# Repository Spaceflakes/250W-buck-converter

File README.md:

# PUDGALA 300
### High-Power-Density 250W Synchronous Buck Converter (28V–60V In → 24.88V @ 10A Out)

> *"Ex umbra, in solem."* — [HEX Aerospace](https://hexaerospace.in)

---

## Overview & Motivation

The **PUDGALA 300** is an open-source, high-power-density synchronous buck converter developed with [HEX Aerospace](https://hexaerospace.in). It steps down wide-range DC voltages (nominal 36V–54V battery buses, 7S–14S LiPo / Li-ion packs) down to a regulated **24.88V (25V / 24V compatible)** rail delivering **10A continuous (250W nominal)**, and has been bench-tested up to **12.5A continuous (~312W)** with peak efficiency exceeding **96%**.

### Field FPV Charging
The primary motivation for this project was powering high-power FPV drone battery chargers directly from repurposed **13S electric scooter (E-scooter) battery packs** in the field.

* **The Problem:** 13S Li-ion battery packs swing from **39.0V** (empty) to **54.6V** (fully charged). However, most popular field chargers (such as ISDT, ToolkitRC, Hota, and SkyRC) have a maximum input voltage limit of **30.0V DC**. Connecting a 13S battery directly would instantly destroy the charger.
* **The Solution:** The PUDGALA 300 steps down the 39V–54.6V input into a stable **24.88V** rail at up to **10A–12.5A (>300W)**. This allows pilots to rapidly parallel-charge multiple 6S drone packs in the field using salvaged e-mobility batteries.

---

> [!CAUTION]
> ### Critical Operational Notice: Anti-Spark Connectors & Inrush Caution
> During early testing of the prototype, the board was connected to a high-voltage 13S battery (~54.6V) with an active load already plugged into the output. The raw XT60 connector sparked violently upon contact, and the severe inrush arc and inductive voltage spike exceeded the MOSFET breakdown rating, killing one of the switching FETs.
>
> **Mandatory Safe Operating Procedures:**
> 1. **Always Use Anti-Spark Connectors:** When connecting sources above 30V (especially 13S / 48V–54.6V packs), use an anti-spark connector with a built-in pre-charge resistor (such as **XT90-S** or **XT60-S**) or an external pre-charge switch.
> 2. **Power-On Sequence:** Always connect the battery input **first** with no output load connected. Confirm the output power indicator LED is on (verifying stable 24.88V regulation) **before** plugging in your charger.
> 3. **Lead Length:** Keep input battery leads as short as possible to minimize parasitic wiring inductance.

---

## Key Specifications

| Parameter | Specification | Notes / Conditions |
| :--- | :--- | :--- |
| **Input Voltage** | **28.0V to 60.0V DC** | Designed for 13S E-scooter packs (39V–54.6V), 7S–14S LiPo, 36V/48V buses |
| **Output Voltage** | **24.88V nominal (~25V)** | Calibrated via precision feedback divider (301 kΩ / 10 kΩ) |
| **Continuous Output Current** | **10.0 A (Nominal) / 12.5 A (Tested)** | 250W nominal; bench-tested to 312W continuous (requires active cooling) |
| **Peak / Overcurrent Limit** | **12.0 A peak** | Cycle-by-cycle limit with automatic hiccup restart |
| **Continuous Output Power** | **250 W nominal (up to 312 W)** | High continuous power density in a pocket-sized 50×50 mm board |
| **Switching Frequency** | **~1.0 MHz (966 kHz nominal)** | Programmed via 9.09 kΩ resistor |
| **Peak Efficiency** | **> 96%** | Typically 94.5%–96.2% across 36V–52V input range |
| **PCB Dimensions** | **50.0 mm × 50.0 mm × 12.0 mm** | Low profile; horizontal bent-lead electrolytic capacitors |
| **PCB Layer Stackup** | **6 Layers (1 oz / 35 µm Cu each)** | Solid internal GND reference planes on L2 & L5 |
| **Connectors** | **AMASS XT30PW-M (Right-Angle)** | High-current, vibration-resistant power in/out connectors |
| **Auxiliary Fan Header** | **2-pin test points (+Fan / -Fan)** | 24V regulated output for an active cooling fan |
| **Enclosure** | **CAD STEP File Coming Soon** | 3D-printable / CNC enclosure in progress |

---

## System Architecture & Block Diagram

```mermaid
flowchart LR
    subgraph Input_Stage ["Input Stage (13S Battery: 39V - 54.6V)"]
        BATT["13S E-Scooter Pack\n(Anti-Spark XT90-S)"] --> J1["Power In\nXT30PW-M"]
        J1 --> D2["TVS Surge Clamp\nSMBJ60A (60V)"]
        D2 --> C_IN_BULK["Bulk Damping\n47µF Elec. (C9)"]
        C_IN_BULK --> C_IN_HF["High-Freq MLCC\n2x 22µF 2220 + 100nF"]
    end

    subgraph Power_Stage ["Synchronous Buck Stage"]
        C_IN_HF --> Q1["High-Side NexFET\nCSD19534Q5A (100V)"]
        Q1 --> SW["Switch Node (SW)"]
        Q2["Low-Side Sync NexFET\nCSD19502Q5B (80V, 2.8mΩ)"] --- SW
        SW --> L1["Molded Power Choke\n2.2µH 20A (BMRF)"]
        L1 --> RSENSE["Current Shunt\n5mΩ 2512 (R3)"]
    end

    subgraph Controller_Loop ["Control & Protection (LM5149-Q1)"]
        U1["TI LM5149-Q1\nSync Controller"] -.->|HO Drive| Q1
        U1 -.->|LO Drive| Q2
        RSENSE -.->|Kelvin ISNS±| U1
        U1 -.->|DRSS Active| R2["CNFG: 40.2kΩ"]
        U1 -.->|1 MHz Osc| R1["RT: 9.09kΩ"]
        U1 -.->|PFM / Diode Emul.| VDDA["VDDA"]
    end

    subgraph Output_Stage ["Output Filtering & Protection (24.88V / 10A-12.5A)"]
        RSENSE --> C_OUT_HF["MLCC Bank\n4x 10µF 1210"]
        C_OUT_HF --> C_OUT_BULK["Output Bulk\n220µF Elec. (C10)"]
        C_OUT_BULK --> D3["OVP TVS Clamp\nSMBJ28A (28V)"]
        D3 --> FB_DIV["Feedback Divider\n301kΩ / 10kΩ"] -.->|FB| U1
        D3 --> LED_IND["Power Good LED\n(D1 + R8 11.5k)"]
        D3 --> J2["Power Out\nXT30PW-M"] --> CHARGER["FPV Charger\n(< 30V Input Limit)"]
        D3 --> FAN_HDR["Fan Header\n(+Fan / -Fan)"]
    end

    classDef stage fill:#1e1e24,stroke:#4a90e2,stroke-width:2px,color:#ffffff;
    classDef controller fill:#2c3e50,stroke:#e74c3c,stroke-width:2px,color:#ffffff;
    class Input_Stage,Power_Stage,Output_Stage stage;
    class Controller_Loop controller;
```

---

## Component Analysis & IC Explanations

### 1. Primary Controller: Texas Instruments LM5149-Q1 (`U1`)
The **LM5149-Q1** (`PLM5149QRGYRQ1`) is an AEC-Q100 qualified, 80V/100V-capable synchronous buck DC-DC controller designed for high-efficiency, low-EMI industrial and automotive applications.
* **Dual-Random Spread Spectrum (DRSS):** Programmed via a 40.2 kΩ resistor (`R2`) on the `CNFG` pin. DRSS modulates the switching frequency to spread out noise energy and lower peak EMI spikes.
* **1.0 MHz Switching Frequency:** Set via a 9.09 kΩ resistor (`R1`) on the `RT` pin (~966 kHz nominal). Running at 1 MHz allows using a small 2.2 µH inductor and compact ceramic capacitors while keeping transient response fast.
* **PFM / Light-Load Efficiency:** The `PFM/SYNC` pin is tied directly to `VDDA`. Under light or no-load conditions, the controller automatically enters diode emulation to reduce idle battery drain.
* **Current Sensing & Protection:** Cycle-by-cycle current limiting using differential sense inputs (`ISNS+` and `VOUT/ISNS-`) across the shunt resistor, cutting off overcurrents at 12A with automatic hiccup restart under short circuits.
* **Gate Drivers & Internal VCC:** Built-in 5V regulator with a 2.2 µF bypass capacitor (`C8`), providing strong gate drive currents and adaptive deadtime control to prevent shoot-through.

---

### 2. High-Side Power MOSFET: TI CSD19534Q5A (`Q1`)
* **Package:** SON 5 mm × 6 mm (TDSON-8)
* **Key Ratings:** 100V, 44A continuous, 10.3 mΩ typical on-resistance
* **Why this part:** Chosen for its ultra-low gate charge (13.8 nC). At a high 1.0 MHz switching frequency, low gate charge is critical to keep switching losses minimal.

---

### 3. Low-Side Synchronous Rectifier MOSFET: TI CSD19502Q5B (`Q2`)
* **Package:** SON 5 mm × 6 mm (TDSON-8)
* **Key Ratings:** 80V, 138A, ultra-low 2.8 mΩ typical on-resistance
* **Why this part:** The low-side switch handles freewheeling current roughly 50% of the time. Its tiny 2.8 mΩ resistance keeps conduction heat minimal (~0.15W at 10A), allowing it to run cool without extra heatsinks.

---

### 4. Power Inductor: Chilisin BMRF00101040 (`L1`)
* **Value:** 2.2 µH, 20A saturation current
* **Why this part:** High 20A saturation rating provides clean headroom above the 12A peak limit. The fully shielded composite iron-powder core prevents radiated magnetic noise from interfering with nearby electronics.

---

### 5. Current Sense Shunt: 5 mΩ Metal Element 2512 (`R3`)
* **Value:** 5 mΩ (0.005 Ω), 1% tolerance, 2512 package
* **Operation:** Senses output current directly. Paired with the controller's 60 mV threshold, it sets the cycle-by-cycle peak limit to 12.0A. Connected using 4-wire Kelvin traces (`NT1`, `NT2`) to avoid PCB trace resistance errors.

---

### 6. Protection Clamps: SMBJ60A & SMBJ28A TVS Diodes
* **Input TVS (`D2` — SMBJ60A):** 60V standoff voltage clamp that absorbs inductive voltage spikes when connecting or disconnecting the battery.
* **Output TVS (`D3` — SMBJ28A):** 28V standoff voltage clamp that prevents the output from ever exceeding the 30V maximum input rating of downstream FPV chargers.
* **Fuse Recommendation:** Always install an inline 15A fuse on the positive battery lead (or use a battery pack with a short-circuit-protected BMS). If an overvoltage fault occurs, the TVS clamps the rail to ground and blows the fuse instantly, ensuring the charger never sees excessive voltage.

---

### 7. Capacitor Filtering Network
* **Input Bank:** Two 22 µF 2220 MLCCs (`C1`, `C2`) for high-frequency ripple, a 100 nF MLCC (`C14`) right at the high-side FET drain, and a 47 µF horizontal electrolytic (`C9`) to damp input line ringing.
* **Output Bank:** Four 10 µF 1210 MLCCs (`C4`, `C11`, `C12`, `C13`) yielding 40 µF of ultra-low ESR capacitance for low voltage ripple, plus a 220 µF horizontal electrolytic (`C10`) for transient load response.

---

## Operating Limits & Thermal Behavior

### 1. Continuous 12.5A Bench Testing
The PUDGALA 300 was successfully tested on the bench at **12.5 A continuous** at ~24.9V, delivering **~312 W output power**:
* **Thermal Rise:** Resistive heating increases significantly (+56%) when stepping up from 10A to 12.5A. In open still air at 12.5A, the bare board components quickly reach 90°C–100°C.
* **Cooling Requirement:** While the board handles 12.5A electrically, **active forced airflow or heatsink coupling is mandatory** for sustained operation above 10A.

### 2. Cooling Options
1. **Passive Air:** Suitable for continuous loads up to **100W–120W** (around 4A–5A).
2. **Forced Air Cooling:** Full **250W–300W+ continuous** rating when a 24V cooling fan is connected to the onboard `+Fan / -Fan` solder pads.
3. **Chassis / Heatsink Mounting:** The bottom side of the PCB has **no components** ("*Yes, there's nothing on this side*"). A 1.0 mm thermal silicone pad placed between the bottom ground plane and an aluminum enclosure or frame allows sinking heat directly into external metal.
4. **Protective Enclosure:** A custom 3D-printable / CNC enclosure STEP model with fan mounting and heatsink interface will be uploaded to this repository soon.

---

## 6-Layer PCB Stackup & Layout

The board uses a custom 6-layer FR4 stackup (1.6 mm thickness, 1 oz / 35 µm copper across all layers) optimized for low loop inductance and thermal dissipation.

| Layer | Type | Material | Thickness | Description & Key Nets |
| :--- | :--- | :--- | :--- | :--- |
| **Top (Layer 1)** | Copper | 1 oz Cu | 35 µm | Components, switching loop, gate drives, analog ground (`F.Cu`) |
| *Dielectric 1* | Prepreg | FR4 | 100 µm (0.10 mm) | Ultra-thin dielectric for tight RF coupling to ground |
| **Inner 1 (Layer 2)** | Copper | 1 oz Cu | 35 µm | **Solid Ground Plane** — immediate return path under L1 (`In1.Cu`) |
| *Dielectric 2* | Core | FR4 | 535 µm (0.535 mm) | Internal structural core |
| **Inner 2 (Layer 3)** | Copper | 1 oz Cu | 35 µm | Ground & auxiliary shielding plane (`In2.Cu`) |
| *Dielectric 3* | Prepreg | FR4 | 100 µm (0.10 mm) | Prepreg isolation layer |
| **Inner 3 (Layer 4)** | Copper | 1 oz Cu | 35 µm | **Power Planes** — +BATT input & +24V distribution (`In3.Cu`) |
| *Dielectric 4* | Core | FR4 | 535 µm (0.535 mm) | Internal structural core |
| **Inner 4 (Layer 5)** | Copper | 1 oz Cu | 35 µm | **Solid Ground Plane** — plane shielding & thermal spreading (`In4.Cu`) |
| *Dielectric 5* | Prepreg | FR4 | 100 µm (0.10 mm) | Prepreg isolation layer |
| **Bottom (Layer 6)** | Copper | 1 oz Cu | 35 µm | **Flat Ground Plane** — zero components, heatsink interface (`B.Cu`) |

*Total Board Thickness: 1.6 mm*

---

## Hardware Gallery

### Assembled & Bare PCB
| Populated SMD Board | Bare 6-Layer ENIG PCB |
| :---: | :---: |
|  |  |
| *Reflowed SMD components on hotplate* | *Bare 50x50 mm board with ENIG finish* |

### PCB Artwork & Stencil Inspection
| Copper Signature Detail | Silkscreen Motto & Fan Header | Solder Paste Deposition (Microscope) |
| :---: | :---: | :---: |
|  |  |  |
| *"Sid J" etched in top copper* | *"Ex umbra, in solem." & fan pads* | *Solder paste stencil on VQFN-24* |

### 3D CAD Renders & Schematic
| Isometric 3D View | Top Component Placement | Bottom Heatsink Plane |
| :---: | :---: | :---: |
|  |  |  |
| *3D isometric view* | *Component layout* | *Flat ground interface* |

> 📄 **Schematic:** Full vector schematic available at [`images/schematic.svg`](images/schematic.svg).

---

## Bill of Materials (BOM)

All components are standard, readily sourcable parts with matching **LCSC Part Numbers** for turn-key assembly via JLCPCB, PCBWay, or other assembly houses.

| Designator | Value / Part | Description | Package / Footprint | Qty | LCSC Part # |
| :--- | :--- | :--- | :--- | :---: | :--- |
| **U1** | **PLM5149QRGYRQ1** | TI 80V/100V Synchronous Buck DC-DC Controller with DRSS | VQFN-24 (4.5×3.5mm) | 1 | **C7528454** |
| **Q1** | **CSD19534Q5A** | TI 100V 44A 10.3mΩ N-Ch NexFET (High-Side Switch) | TDSON-8 / SON 5×6mm | 1 | **C114200** |
| **Q2** | **CSD19502Q5B** | TI 80V 138A 2.8mΩ N-Ch NexFET (Low-Side Sync Rectifier) | TDSON-8 / SON 5×6mm | 1 | **C2864118** |
| **L1** | **2.2u, 20A** | Chilisin BMRF00101040 Shielded Power Inductor | SMD 10×10×4.0mm | 1 | **C3002681** |
| **R3** | **5m (0.005Ω)** | Current Sense Shunt Resistor, 1%, 2W/3W | SMD 2512 | 1 | **C48982662** |
| **D2** | **SMBJ60A** | 600W 60V Unidirectional TVS Surge Diode | DO-214AA (SMB) | 1 | *Standard* |
| **D3** | **SMBJ28A** | 600W 28V Unidirectional TVS Overvoltage Diode | DO-214AA (SMB) | 1 | *Standard* |
| **J1** | **Power In** | AMASS XT30PW-M Right-Angle 2-Pin Male Connector | XT30PW-M Horizontal | 1 | *Standard* |
| **J2** | **Power Out** | AMASS XT30PW-M Right-Angle 2-Pin Male Connector | XT30PW-M Horizontal | 1 | *Standard* |
| **C1, C2** | **22u** | Ceramic Capacitor, 50V/100V, X7R | SMD 2220 | 2 | **C7499406** |
| **C4, C11, C12, C13** | **10u** | Ceramic Capacitor, 35V/50V, X7R | SMD 1210 | 4 | **C77102** |
| **C9** | **47u** | Low-ESR Radial Aluminum Electrolytic, 63V/100V (Horizontal) | Rad 8×15mm Horizontal | 1 | **C5110663** |
| **C10** | **220u** | Low-ESR Radial Aluminum Electrolytic, 35V/50V (Horizontal) | Rad 10×16mm Horizontal | 1 | **C95082** |
| **C3** | **100n** | Bootstrap Capacitor (CBOOT), 50V, X7R | SMD 0603 | 1 | **C15725** |
| **C14** | **100n** | High-Frequency Input Bypass, 100V, X7R | SMD 0603 | 1 | **C7499406** |
| **C5** | **1u** | VDDA Analog Bypass Capacitor, 16V, X7R | SMD 0402 | 1 | **C29266** |
| **C6** | **680p** | Loop Compensation Zero Capacitor, 50V, C0G/X7R | SMD 0402 | 1 | *Standard* |
| **C7** | **24p** | Loop Compensation HF Pole Capacitor, 50V, C0G | SMD 0402 | 1 | **C2171081** |
| **C8** | **2.2u** | VCC Gate Drive Bias Bypass, 16V, X7R | SMD 0805 | 1 | **C170101** |
| **R1** | **9k09 (9.09kΩ)** | Switching Frequency Resistor (1% tolerance, sets ~1MHz) | SMD 0402 | 1 | **C861611** |
| **R2** | **40k2 (40.2kΩ)** | Mode & Dual-Random Spread Spectrum Resistor (1%) | SMD 0402 | 1 | **C491131** |
| **R4** | **301k (301kΩ)** | Feedback Voltage Divider Upper Resistor (0.5% or 1%) | SMD 0402 | 1 | **C2981491** |
| **R5** | **10k (10.0kΩ)** | Feedback Voltage Divider Lower Resistor (0.5% or 1%) | SMD 0402 | 1 | **C95204** |
| **R6** | **5k9 (5.9kΩ)** | External Error Amplifier Compensation Resistor (1%) | SMD 0402 | 1 | **C491142** |
| **R7** | **100k (100kΩ)** | Power Good (PG) Pull-Up Resistor (1%) | SMD 0402 | 1 | **C122538** |
| **R8** | **11k5 (11.5kΩ)** | LED Current Limiting Ballast Resistor (~2mA @ 24V) | SMD 0805 | 1 | *Standard* |
| **D1** | **LED** | Green / Blue Status Indicator LED | SMD 0603 | 1 | **C46610608** |
| **+FAN, -FAN** | **+Fan / -Fan** | Keystone 5015 Micro-Mini Solder Test Points | TP Keystone 5015 | 2 | *Standard* |
| **H1, H2, H3, H4** | **M3 Holes** | Mounting Holes with Grounded Annular Pad & Via Array | 3.2mm M3 Pad | 4 | *Mechanical* |
| **NT1, NT2, NT3** | **NetTie_2** | Kelvin-Sense & AGND Star Ground Isolation Net Ties | Net Tie SMD | 3 | *PCB Feature* |

> An interactive browser-based BOM with cross-probing component highlighting is located at [`250W Bat/bom/ibom.html`](250W%20Bat/bom/ibom.html).

---

## Manufacturing & Fabrication Guide

### PCB Fabrication Parameters
* **Layers:** 6
* **Board Dimensions:** 50.0 mm × 50.0 mm
* **Corner Radius:** 4.0 mm
* **PCB Thickness:** 1.6 mm
* **Copper Weight:** 1 oz outer / 1 oz inner (35 µm Cu across all 6 layers)
* **Surface Finish:** ENIG (Electroless Nickel Immersion Gold) recommended for high-current pads and flat thermal contact; Lead-Free HASL is acceptable.
* **Solder Mask:** Green (or Matte Black)
* **Silkscreen:** White
* **Minimum Trace / Space:** 0.15 mm / 0.15 mm (6 mil / 6 mil)
* **Minimum Drill:** 0.3 mm (via hole) / 0.5 mm (via pad)

### Production Files
All fabrication and assembly deliverables are located in the [`250W Bat/production/`](250W%20Bat/production/) directory:
* **Gerbers & Drill Archive:** [`250W_Bat.zip`](250W%20Bat/production/250W_Bat.zip)
* **BOM File:** [`bom.csv`](250W%20Bat/production/bom.csv)
* **Pick-and-Place (CPL) Centroid:** [`positions.csv`](250W%20Bat/production/positions.csv)
* **Netlist:** [`netlist.ipc`](250W%20Bat/production/netlist.ipc)
* **3D CAD STEP Model:** [`Converter.step`](250W%20Bat/Converter.step) & [`board.step`](250W%20Bat/board.step)

---

## Repository Structure

```
├── LICENSE                         # MIT Open Source License
├── README.md                       # Main project documentation (this file)
├── images/                         # Project graphics, renders, and diagrams
│   ├── pcb_3d_isometric.png        # Raytraced 3D perspective view
│   ├── pcb_3d_top.png              # Raytraced top component view
│   ├── pcb_3d_bottom.png           # Raytraced bottom ground plane view
│   ├── schematic.svg               # Vector schematic export
│   └── irl/                        # Real-world hardware photography
│       ├── README.md               # Photography index and descriptions
│       ├── pcb_bare_board.jpg      # Studio shot of bare ENIG PCB
│       ├── pcb_smd_assembled.jpg   # Populated SMD board post-reflow
│       ├── pcb_signature_detail.jpg# Macro of "Sid J" signature
│       ├── pcb_motto_detail.jpg    # Macro of "Ex umbra, in solem." & fan pads
│       └── microscope_solder_paste_qfn.jpg # Microscope view of VQFN-24 solder paste
└── 250W Bat/                       # KiCad design directory
    ├── 250W Bat.kicad_pro          # KiCad Project file (KiCad v10)
    ├── 250W Bat.kicad_sch          # Main schematic sheet
    ├── 250W Bat.kicad_pcb          # 6-layer board layout
    ├── Converter.step              # Full 3D STEP CAD assembly
    ├── board.step                  # Bare PCB 3D STEP file
    ├── bom/
    │   └── ibom.html               # Interactive HTML Bill of Materials
    └── production/                 # PCBA manufacturing outputs
        ├── 250W_Bat.zip            # Gerber & Excellon drill files
        ├── bom.csv                 # Production BOM with LCSC part numbers
        ├── positions.csv           # SMT pick-and-place centroid data
        └── netlist.ipc             # IPC-D-356 electrical test netlist
```

---

## Author & License

* **Author / Design:** Siddesh Jain
* **License:** Licensed under the permissive **[MIT License](LICENSE)**. You are free to use, modify, distribute, and manufacture this hardware for academic, hobbyist, and commercial projects.

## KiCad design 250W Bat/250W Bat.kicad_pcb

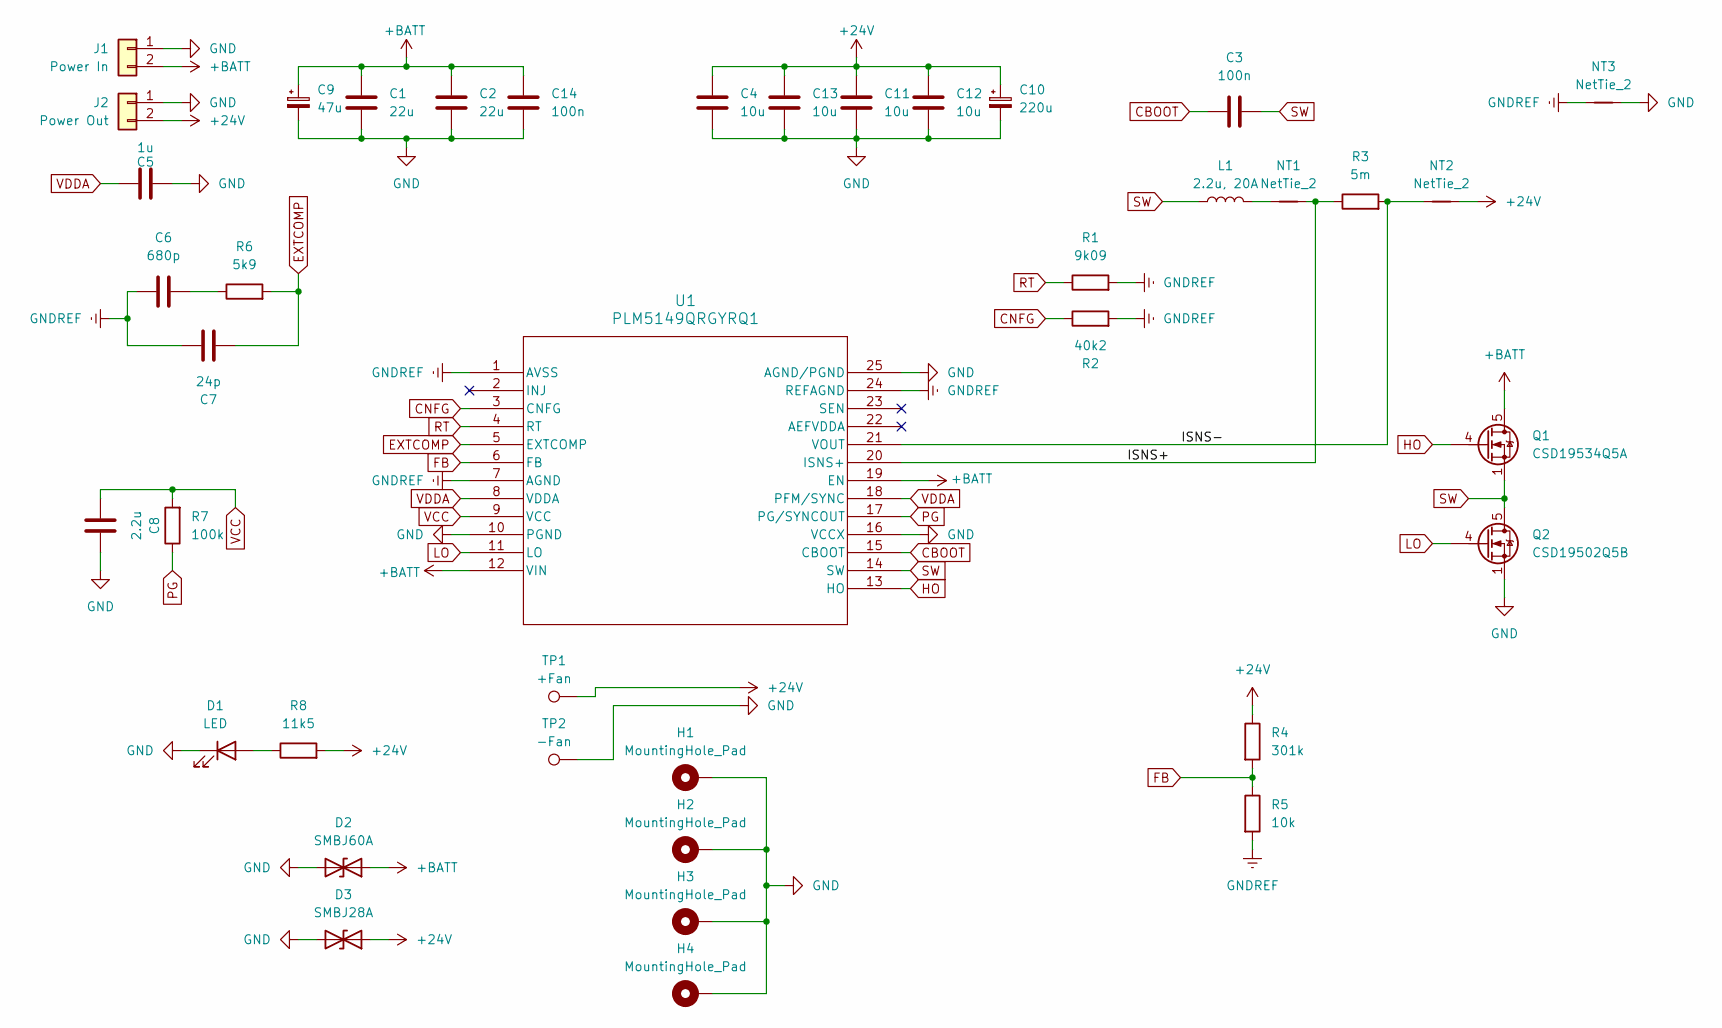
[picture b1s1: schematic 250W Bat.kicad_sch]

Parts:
C1, C2: 22u; C_2220_5750Metric; LCSC C7499406
C3: 100n; C_0603_1608Metric; LCSC C15725
C4, C11, C12, C13: 10u; C_1210_3225Metric; LCSC C77102
C5: 1u; C_0402_1005Metric; LCSC C29266
C6: 680p; C_0402_1005Metric
C7: 24p; C_0402_1005Metric; LCSC C2171081
C8: 2.2u; C_0805_2012Metric; LCSC C170101
C9: 47u; CP_8x15mm_horiz-R; LCSC C5110663
C10: 220u; CP_10x16mm_horiz-R; LCSC C95082
C14: 100n; C_0603_1608Metric; LCSC C7499406
D1: LED; LED_0603_1608Metric; LCSC C46610608
D2: SMBJ60A; D_SMB
D3: SMBJ28A; D_SMB
H1, H2, H3, H4: MountingHole_Pad; MountingHole_3.2mm_M3_Pad_Via
J1: Power In; AMASS_XT30PW-M_1x02_P2.50mm_Horizontal
J2: Power Out; AMASS_XT30PW-M_1x02_P2.50mm_Horizontal
L1: 2.2u, 20A; L_Chilisin_BMRF00101040; LCSC C3002681
NT1, NT2: NetTie_2; NetTie-2_SMD_Pad2.0mm
NT3: NetTie_2; NetTie-2_SMD_Pad0.5mm
Q1: CSD19534Q5A; TDSON-8-1; LCSC C114200
Q2: CSD19502Q5B; TDSON-8-1; LCSC C2864118
R1: 9k09; R_0402_1005Metric; LCSC C861611
R2: 40k2; R_0402_1005Metric; LCSC C491131
R3: 5m; R_2512_6332Metric; LCSC C48982662
R4: 301k; R_0402_1005Metric; LCSC C2981491
R5: 10k; R_0402_1005Metric; LCSC C95204
R6: 5k9; R_0402_1005Metric; LCSC C491142
R7: 100k; R_0402_1005Metric; LCSC C122538
R8: 11k5; R_0805_2012Metric
TP1: +Fan; TestPoint_Keystone_5015_Micro_Mini
TP2: -Fan; TestPoint_Keystone_5015_Micro_Mini
U1: PLM5149QRGYRQ1; VQFN24_RGY_TEX; LCSC C7528454

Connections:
+24V: C4.1, C10.1, C11.1, C12.1, C13.1, D3.1 (A1), J2.2, NT2.2, R4.1, R8.2, TP1.1; also elsewhere on the board
+BATT: C1.1, C2.1, C9.1, C14.1, D2.1 (A1), J1.2, Q1.5 (D), U1.12 (VIN), U1.19 (EN)
/ISNS+: NT1.2, R3.1, U1.20 (ISNS+)
/ISNS-: NT2.1, R3.2, U1.21 (VOUT)
CBOOT: C3.1, U1.15 (CBOOT)
CNFG: R2.1, U1.3 (CNFG)
EXTCOMP: C7.2, R6.2, U1.5 (EXTCOMP)
FB: R4.2, R5.1, U1.6 (FB)
GND: C1.2, C2.2, C4.2, C5.1, C8.2, C9.2, C10.2, C11.2, C12.2, C13.2, C14.2, D1.1 (K), D2.2 (A2), D3.2 (A2), H1.1 (1_1), H2.1 (1_1), H3.1 (1_1), H4.1 (1_1), J1.1, J2.1, NT3.2, Q2.1 (S), Q2.2 (S), Q2.3 (S), TP2.1, U1.10 (PGND), U1.16 (VCCX), U1.25 (AGND/PGND); also elsewhere on the board
GNDREF: C6.1, C7.1, NT3.1, R1.2, R2.2, R5.2, U1.1 (AVSS), U1.7 (AGND), U1.24 (REFAGND)
HO: Q1.4 (G), U1.13 (HO)
LO: Q2.4 (G), U1.11 (LO)
unnamed: C6.2, R6.1
unnamed: D1.2 (A), R8.1
unnamed: L1.2, NT1.1
PG: R7.1, U1.17 (PG/SYNCOUT)
RT: R1.1, U1.4 (RT)
SW: C3.2, L1.1, Q1.1 (S), Q1.2 (S), Q1.3 (S), Q2.5 (D), U1.14 (SW)
VCC: C8.1, R7.2, U1.9 (VCC)
VDDA: C5.2, U1.8 (VDDA), U1.18 (PFM/SYNC)

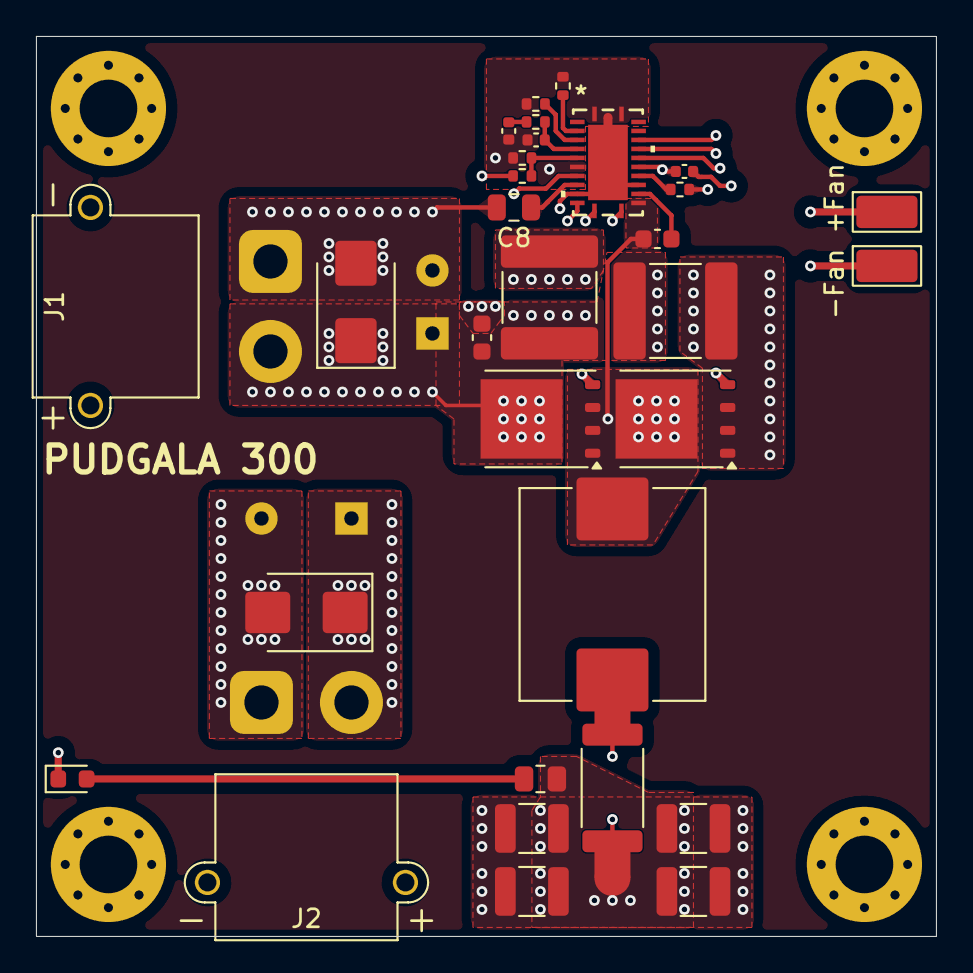
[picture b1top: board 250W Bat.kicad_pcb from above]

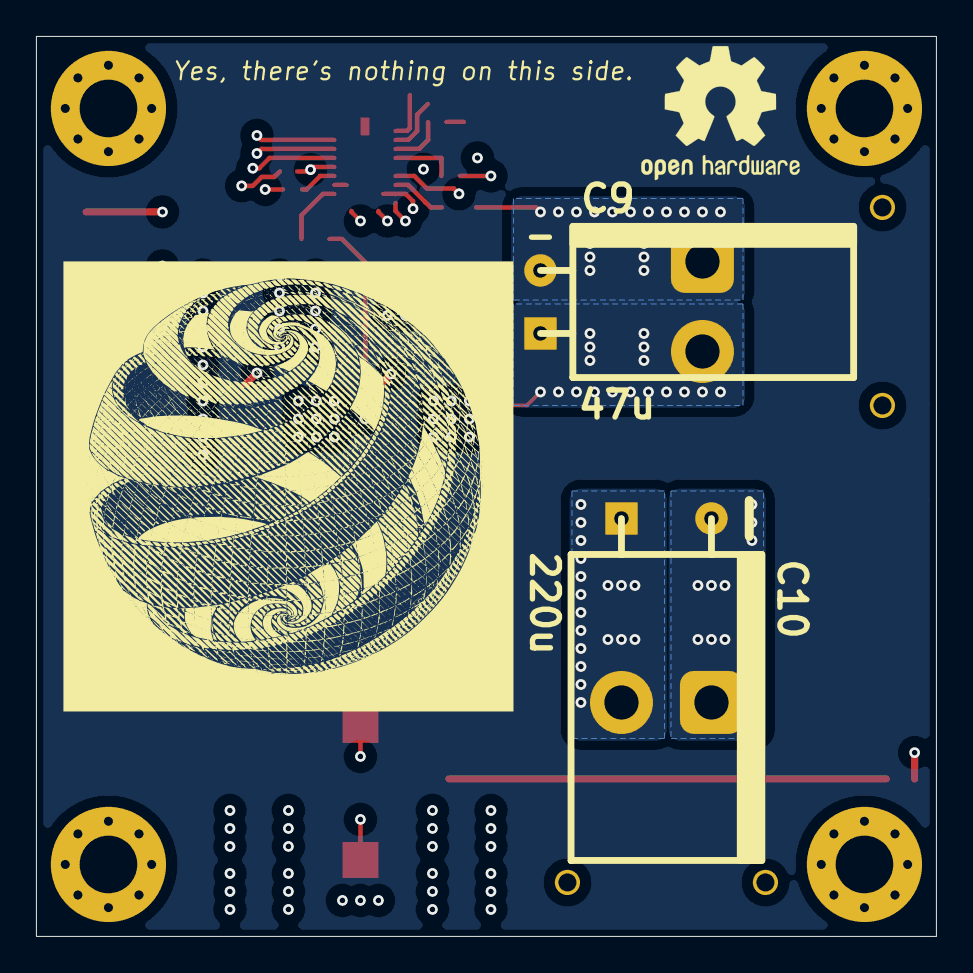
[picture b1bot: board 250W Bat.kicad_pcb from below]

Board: 6 copper layers, 50.0 x 50.0 mm, 40 parts (2 on the bottom side), 20 nets.

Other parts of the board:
+Fan: +Fan; TestPoint_Keystone_5015_Micro_Mini
-Fan: -Fan; TestPoint_Keystone_5015_Micro_Mini

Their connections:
+24V: +Fan.1 (1_1); also elsewhere on the board
GND: -Fan.1 (1_1); also elsewhere on the board
